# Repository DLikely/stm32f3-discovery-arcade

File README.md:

#STM32F3-Discovery Arcade control interface

An arcade controls interface board implementing a multireport USB HID device with 4
Joysticks connected by GPIO to an STM32F3 Discovery board.

This application is forked from the cjheath's
[stm32f3-discovery-usb-example-project](cjheath/stm32f3-discovery-usb-example.git),
which in turn is derived from the template application for the STM32F30x ARM
microcontrollers that compiles with GNU tools.

The template serves as a quick-start for those who do not wish to use an IDE, but rather
develop in a text editor of choice and build from the command line. It is
derived from [mblythe's version](https://github.com/mblythe86/stm32f3-discovery-basic-template),
which also credits other sources.

## Installing

Before building, you should install the GNU compiler tools.  I'm using the
ARM-supported [Launchpad gcc-arm-embedded](https://launchpad.net/gcc-arm-embedded)
toolchain, installed in **/usr/local/arm**.

The package expects a patched and compiled version of the [STM32F3 standard
peripherals and drivers library](http://www.st.com/web/en/catalog/tools/PF258154)
to be in an adjacent directory. Download the ZIP file, unzip it to the parent
directory above this one, and change into the new **STM32F3-Discovery_FW_V1.1.0**
directory and say:

    patch -p1 < ../stm32f3-discovery-usb-example/STM32F3-Discovery_FW_V1.1.0-gcc.patch

This should cleanly apply the patch to a number of files. Then say:

    make install

This should create an **inst** directory (under the top-level ST firmware
directory) containing two compiled code libraries and copies of all header files
required to build applications.

Now change back to this application template directory and build the application by saying:

    make

You should see five new files whose names start with *main*. These are your
executables and program listings and symbol maps.

##Source code
The **src** directory contains the source-code files for this application template.

**system_stm32f30x.c** can be re-generated using an Excel (.XLS) file developed
by ST. This sets up the system clock values for the project. The file included
in this repository is taken from the STM32F3-Discovery firmware package. It is
copied from the directory: **Libraries/CMSIS/Device/ST/STM32F30x/Source/Templates/**

##Programming and debugging code on the board

First, make sure you have OpenOCD installed and in your path. Then connect your
board, and load the application by saying:

    make program

This task relies on the OpenOCD script provided in the **extra** directory.

To load the program and debug it using GDB in TUI mode, simply say

    make debug

This relies on a gdb script which is also in the **extra** directory.
See [this blog post](http://www.mjblythe.com/hacks/2013/02/debugging-stm32-with-gdb-and-openocd/)
for info about how it works.

##Installing OpenOCD

Assuming you have your ARM gcc tools installed in **/usr/local/arm**, you
probably want to install OpenOCD there too. Change these instructions and the
Makefile if you want it elsewhere. After you have cloned the [OpenOCD
repository](http://openocd.git.sourceforge.net/git/gitweb.cgi?p=openocd/openocd;a=summary),
use these commands to compile and install it (it must be configured with stlink
support enabled):

    ./bootstrap
    ./configure --prefix=/usr/local/arm --enable-maintainer-mode --enable-stlink
    make 
    sudo make install

If there is an error finding the .cfg file, please double-check the
OPENOCD_BOARD_DIR constant in the Makefile.

###UDEV Rule for the Discovery Board

If you are not able to communicate with the STM32F3-Discovery board without
root privileges you should add a udev rule for this hardware by following
[these steps from the stlink repo readme file](https://github.com/texane/stlink#readme).

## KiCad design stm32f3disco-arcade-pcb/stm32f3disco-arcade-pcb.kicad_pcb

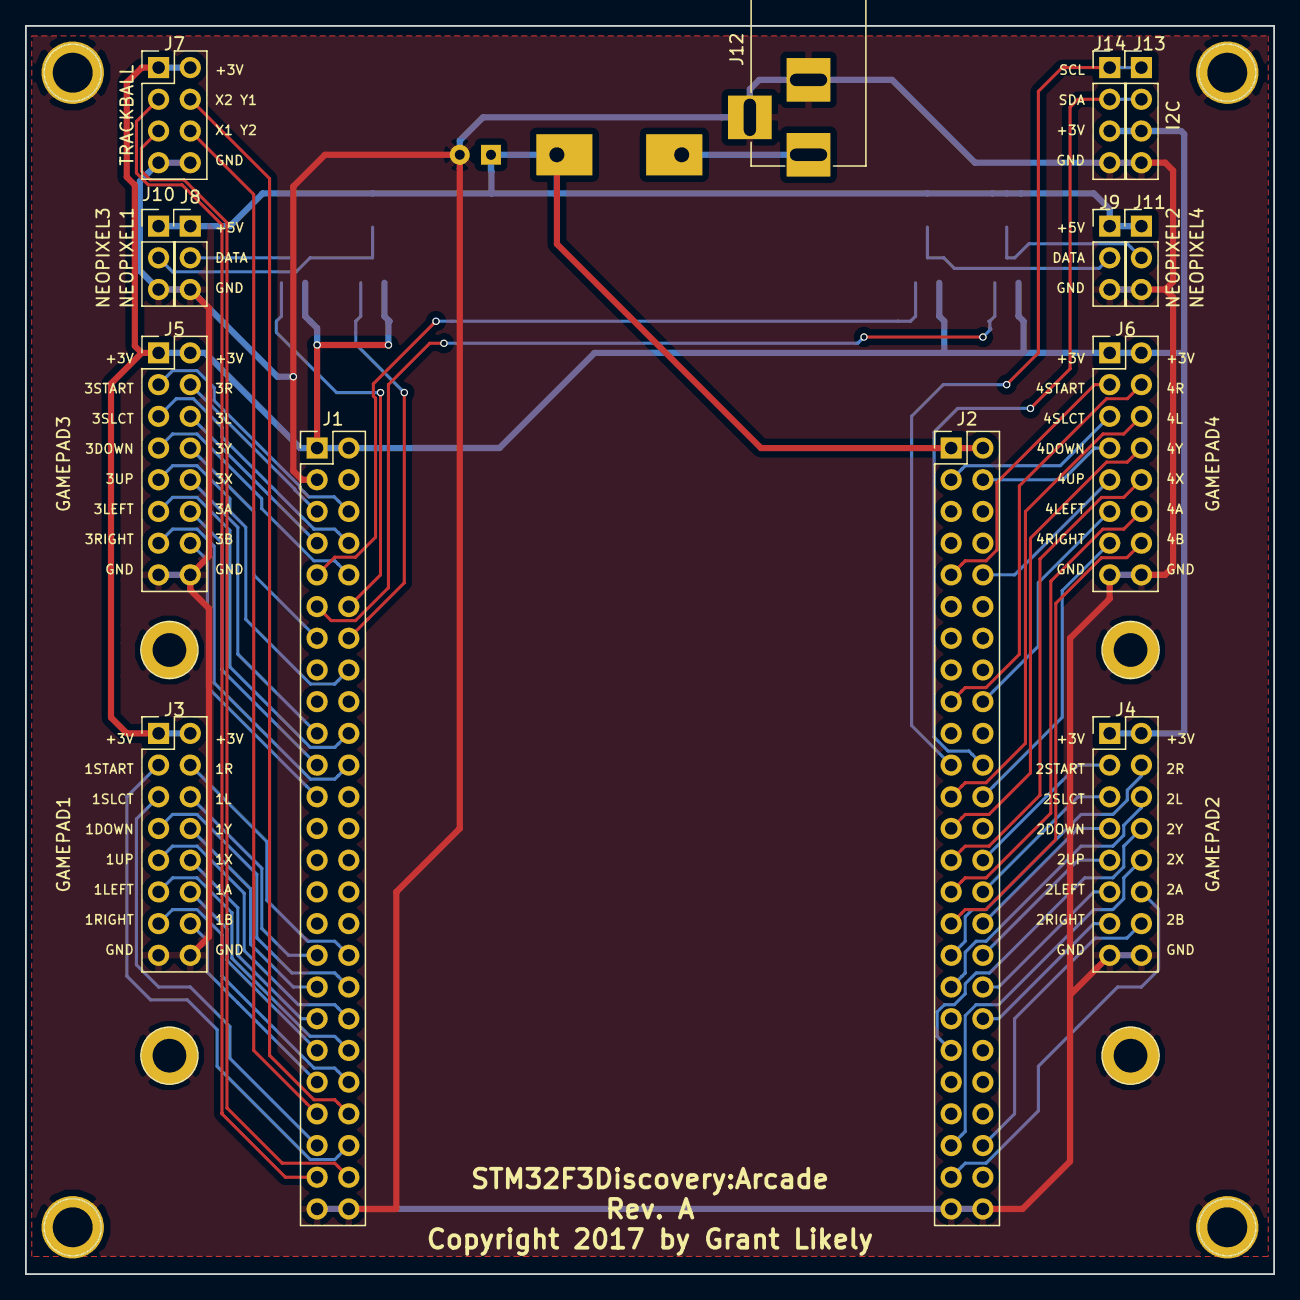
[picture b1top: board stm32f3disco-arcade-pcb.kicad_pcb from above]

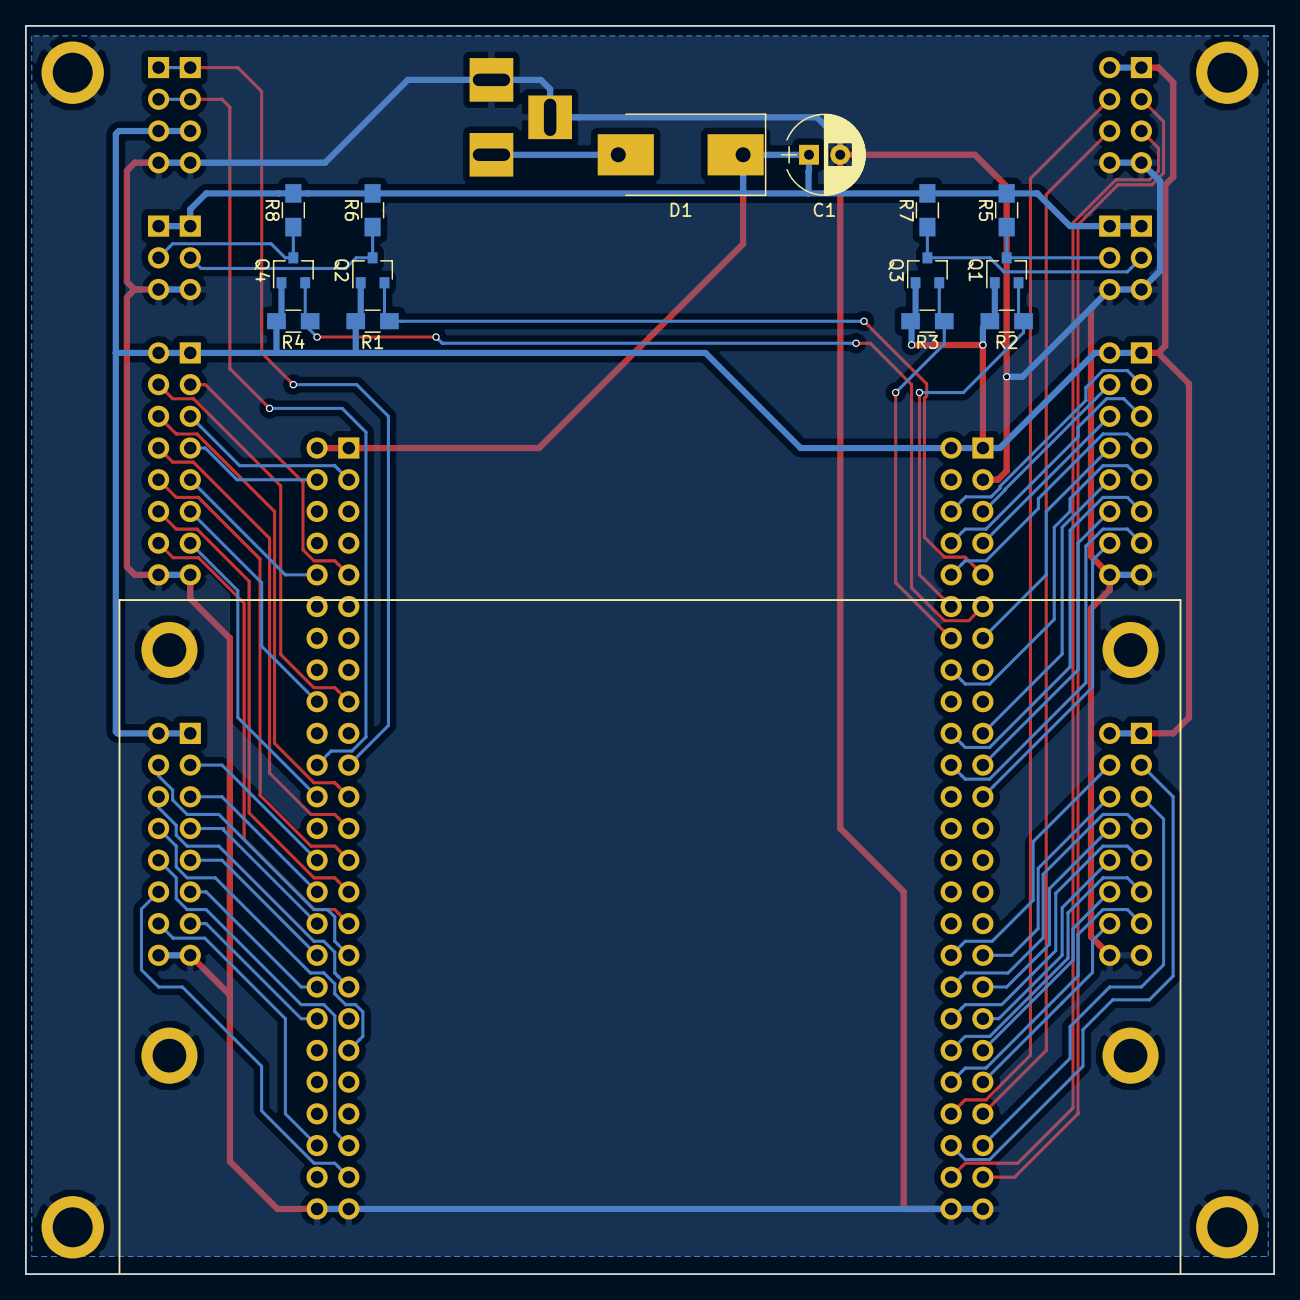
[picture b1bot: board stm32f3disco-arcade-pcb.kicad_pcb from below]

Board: 2 copper layers, 100.0 x 100.0 mm, 36 parts (14 on the bottom side), 66 nets.

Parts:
C1: 1000uF; CP_Radial_D6.3mm_P2.50mm
D1: D; D_SMC-RM10_Universal_Handsoldering
H1, H2, H3, H4: MountingHole_3.2mm_M3; 1pin
H5, H6, H7, H8: MountingHole_2.7mm_M2.5; 1pin
J1: STM32F3DISCO_P1; Pin_Header_Straight_2x25_Pitch2.54mm
J2: STM32F3DISCO_P2; Pin_Header_Straight_2x25_Pitch2.54mm
J3: GAMEPAD1; Pin_Header_Straight_2x08_Pitch2.54mm
J4: GAMEPAD2; Pin_Header_Straight_2x08_Pitch2.54mm
J5: GAMEPAD3; Pin_Header_Straight_2x08_Pitch2.54mm
J6: GAMEPAD4; Pin_Header_Straight_2x08_Pitch2.54mm
J7: TRACKBALL; Pin_Header_Straight_2x04_Pitch2.54mm
J8: NEOPIXEL1; Pin_Header_Straight_1x03_Pitch2.54mm
J9: NEOPIXEL2; Pin_Header_Straight_1x03_Pitch2.54mm
J10: NEOPIXEL3; Pin_Header_Straight_1x03_Pitch2.54mm
J11: NEOPIXEL4; Pin_Header_Straight_1x03_Pitch2.54mm
J12: BARREL_JACK
J13, J14: I2C; Pin_Header_Straight_1x04_Pitch2.54mm
Q1, Q2, Q3, Q4: BSS138; SOT-23
R1, R2, R3, R4, R5, R6, R7, R8: 10k; R_0805_HandSoldering

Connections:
+3V3: J1.1, J1.2, J3.1, J3.2, J4.1, J4.2, J5.1, J5.2, J6.1, J6.2, J7.1, J7.2, J13.3, J14.3, Q1.1, Q2.1, Q3.1, Q4.1, R1.2, R2.2, R3.2, R4.2
+5V: C1.1, D1.1, J2.1, J2.2, J8.1, J9.1, J10.1, J11.1, R5.2, R6.2, R7.2, R8.2
+5VA: D1.2, J12.1
/P1A: J1.41, J3.14
/P1B: J1.39, J3.12
/P1DOWN: J1.36, J3.7
/P1L: J1.33, J3.6
/P1LEFT: J1.40, J3.11
/P1R: J1.34, J3.4
/P1RIGHT: J1.42, J3.13
/P1SLCT: J1.45, J3.5
/P1STRT: J1.46, J3.3
/P1UP: J1.38, J3.9
/P1X: J1.37, J3.10
/P1Y: J1.35, J3.8
/P2A: J2.46, J4.14
/P2B: J2.47, J4.12
/P2DOWN: J2.32, J4.7
/P2L: J2.35, J4.6
/P2LEFT: J2.36, J4.11
/P2R: J2.33, J4.4
/P2RIGHT: J2.38, J4.13
/P2SLCT: J2.30, J4.5
/P2STRT: J2.28, J4.3
/P2UP: J2.34, J4.9
/P2X: J2.45, J4.10
/P2Y: J2.39, J4.8
/P3A: J1.23, J5.14
/P3B: J1.21, J5.12
/P3DOWN: J1.10, J5.7
/P3L: J1.7, J5.6
/P3LEFT: J1.20, J5.11
/P3R: J1.5, J5.4
/P3RIGHT: J1.22, J5.13
/P3SLCT: J1.8, J5.5
/P3STRT: J1.6, J5.3
/P3UP: J1.16, J5.9
/P3X: J1.19, J5.10
/P3Y: J1.13, J5.8
/P4A: J2.31, J6.14
/P4B: J2.29, J6.12
/P4DOWN: J2.4, J6.7
/P4L: J2.23, J6.6
/P4LEFT: J2.18, J6.11
/P4R: J2.17, J6.4
/P4RIGHT: J2.24, J6.13
/P4SLCT: J2.3, J6.5
/P4STRT: J2.9, J6.3
/P4UP: J2.10, J6.9
/P4X: J2.27, J6.10
/P4Y: J2.25, J6.8
GND: C1.2, H1.1, H2.1, H3.1, H4.1, H5.1, H6.1, H7.1, H8.1, J1.3, J1.49, J1.50, J2.49, J2.50, J3.15, J3.16, J4.15, J4.16, J5.15, J5.16, J6.15, J6.16, J7.7, J7.8, J8.3, J9.3, J10.3, J11.3, J12.2, J12.3, J13.4, J14.4
unnamed: J8.2, Q1.3, R5.1
unnamed: J9.2, Q2.3, R6.1
unnamed: J10.2, Q3.3, R7.1
unnamed: J11.2, Q4.3, R8.1
PWM0: J1.12, Q1.2, R2.1
PWM1: J1.9, Q2.2, R1.1
PWM2: J1.14, Q3.2, R3.1
PWM3: J1.11, Q4.2, R4.1
SCL: J2.21, J13.1, J14.1
SDA: J2.22, J13.2, J14.2
TBALL_X1: J1.48, J7.5
TBALL_X2: J1.47, J7.3
TBALL_Y1: J1.44, J7.4
TBALL_Y2: J1.43, J7.6

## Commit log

2017-09-10 Refactor to provide 4 gamepad interfaces
    Refactored the project to be used as an Arcade control panel interface.
    This commit changes it to be a multireport hid device with 4 GPIO
    connected joysticks. Still to be added is a trackball interface and
    control of WS2812 NeoPixels RGB LEDs.
2017-09-10 Initial support for NeoPixel LED illumination
    Add support for NeoPixels attached to TIM2. This patch just associates
    LEDs with buttons and lights the LED when the button is pressed. Next
    step will be to add output reports for setting the LED state.
2017-09-10 Fix button assignments and Y axis direction
    The y axis was oriented the wrong way. Positive values mean up, not
    down. Also reorder the buttons to match the Buffalo gamepad. Button
    order is now: A,B,X,Y,L,R,Select,Start.
2017-09-10 Add trackball support with TIM3/4 quatrature mode
    Enable TIM3 and TIM4 in encoder mode to use as a mouse, and add another
    report ID for the mouse reports. The joystick pins were also moved to
    free up the pins attached to TIM3/4. This change is reflected in main.c
2017-09-10 Update README to describe the arcade interface project
2017-09-10 Default to button LEDs being on instead of off.
    Change default to light all the LEDs, and to turn them off when the
    associated button is pressed.
2017-09-10 Add PCB KiCad project
    This is an adaptor PCB design for the STM32F3-Discovery board to make
    wiring up arcade controls simpler and tidier, as well as allowing for
    external power.
2017-09-10 Set button mappings for stm32f3disco-arcade adapter
    The custom arcade adaptor board is being used now and some of the GPIO pin
    mappings have changed. All the LED mappings have changed too as well as
    being changed to SK6812 RGBW modules. Change the button mapping to match
    the hardware.
2017-09-10 Fix UART pin assignment for STM32F3-Discovery
    The STM32F3 Discovery user manual incorrectly says that USART1 is mapped
    to PA9/10. It is not. It is mapped to PC4/5 instead, which requires a
    change to the board design so that USART console output can be used.
2017-09-10 Add mouse click actions
    Make some of the arcade buttons dual purpose by generating mouse click
    events in addition to button presses. This may be a little hacky, but it
    is a reasonable first step. However, this commit exposes a problem with
    the way event reports are handled. Frequently reports get lost which
    results in lost button presses. This will need to be fixed, probably by
    explicitly waiting for the previous USB report to complete sending
2017-09-10 Add color effect to trackball
    Adds support for illuminating the trackball with a 7-pixel NeoPixel
    'Jewel' daisy chained to end of the player 2 & 4 LED string. As the
    trackball is rolled, the color changes using the common NeoPixel wheel()
    function.
2017-09-10 Fix x-axis polarity on trackball
    It was reversed.
2017-09-10 Enable all 4 NeoPixel channels
    Enable driving NeoPixels on all 4 NeoPixel outputs, aka all 4 output
    channels of TIM1 in PWM mode. The TIM device supports writing to
    multiple registers on each DMA trigger. The driver uses this to load the
    transmit buffer with PWM values for each of the output pins.
    There is still only one buffer for NeoPixel colour data, but now it is
    divided into 4, with each channel assigned a quarter of the buffer. So,
2017-09-10 Add macros to simplify setting LED color and location
    The color and location of buttons can change for each different arcade
    panel build. To make it easier to change the configuration, move the
    values into a new set of #defines at the top of main.c
2017-09-10 Update to RGBW NeoPixels
    Fix the code to work for 32-bit RGBW NeoPixels instead of 24-bit RGB.
    This is a hard-coded fix to get RGBW working. Future change will be to
    make the code runtime configurable between 24 and 32 bit pixels.
2017-09-10 trivial: fix indentation
2017-09-10 Add the Adafruit NeoPixel library to hack on
    The Adafruit NeoPixel library is the most popular API for the pixels,
    and it already supports all the variants. Add the Adafruit code so that
    STM32 support can be added.
2017-09-12 Only refresh gamepad reports when the report can actually be sent
    The gamepad reports were getting refreshed every time through the loop,
    but reports are only generated every 5th time through. To make sure data
    doesn't get dropped, only refresh the report on a cycle when it can
    actually be sent.
2017-09-12 Fix missed reports bug
    Wait for the previous transfer to complete before kicking off another
    one and fix the wait loop so that the main loop doesn't get stuck
    waiting for a particular value of the DataReady timer counter.
2017-09-13 Use a VID/DID pair that sets HID_QUIRK_MULTI_REPORT in Linux
    Linux doesn't handle multiple joystick devices well. It tries to make
    the all a single joystick. Use someone elses VID/DID to get the
    multireport quirk turned on when the device is plugged in.
2017-09-13 Fix y axix polarity (again)
    Repeat after me. Up is negative, down is positive.
    Signed-up-by: Grant Likely <grant.likely@secretlab.ca>
2017-09-16 Fix powerup problem with USB
    Insert a delay on making the USB lines active so that the powerup
    sequence doesn't cause USB to fail to enumerate
2017-09-17 Handle all of the USB HID protocol
    Implement the rest of the HID protocol so that the device responds
    correctly when the host sets/gets idle, and when it fetches the get
    reports.
2017-09-17 Update USB descriptors to better describe the device
    Little changes to the USB HID descriptor.
    - Change max power to 480mA
    - Update HID Spec version to v1.1
    - Change max report size to 8
2017-09-17 Clean up indentation on main.c and add ws2812 header
2017-09-17 Move things around to get rid of main.h
    Nothing from main.c is called from anywhere else. There is no purpose to
    having a main.h. Move the function declarations out of that file and
    delete it. Also move main() to the bottom of main.c so that it doesn't
    need any forward function declarations either.
2017-09-17 Cleanup usb_desc.[ch]
    Clean up the indentation and comments on usb_desc files.
2017-09-17 Move Accelerometer code to another file
2017-09-18 Cleanup usb_prop.[ch] indentation
2017-09-18 Cleanup usb_desc.[ch] to not export as much
    To improve general code sanitation, remove as much as possible from
    usb_desc.h and only export what is necessary.
2017-09-18 Restrict PrevXferComplete to main.c
    main.c is the only place that PrevXferComplete needs to be used.
2017-09-18 Clean up usb_istr.[ch]
2017-09-19 Check the status of all controls every loop
    The main loop was very naively only updating one of the 5 reports every
    time through which is less than ideal. It should be checking all of them
    and making sure every report that has data gets sent out each time
    through.
2017-09-19 Move color helpers to ws2812.h
    The color macros are part of the ws2812.c code. Move it out of main.c
    where it doesn't belong.
2017-09-19 Store color values in a u32
    Use u32 values for storing colors. A u32 is independent from the pixel
    format, and this code needs to support both RGB and RGBW pixels. Using a
    u32 means the color value doesn't change depending on the pixel type.
2017-09-19 Consistently use #defined values with dereferencing pixel data
    Clean up the neopixel buffer references to use a helper function for
    dereferencing specific pixels in the buffer
2017-09-19 Switch to byte-oriented pixel buffer
    Change the code from an array of fixed size pixels to a flat buffer that
    can have the pixels mapped wherever they need to be. This allows both
    RGB and RGBW pixels to be supported at the same time, and even connected
    to the same channel.
2017-09-25 Abstract out neopixel strip properties
    Factor out the neopixel handling that was hard coded into main.c and
    make it a proper set of helper functions. This makes it possible to
    support multiple pixel formats from the same firmware and the main code
    doesn't need to calculate each pixel's offset in the frame buffer.
2017-09-25 Add physical position information about the pixels
    The physical pixel locations will be used to create animations across
    the arcade panel.
2017-09-26 Add a simple RGB animations engine
    Add a simple animation engine for the Neopixels. The engine only knows
    how to do two things. It can display each of the player's assigned
    colours, or it can cycle through the rainbow in a variety of patterns.
    Changing modes is accomplished by pressing the P4 "start & select"
    buttons at the same time.
    There is lots of room to improve the display effects, and it would look
2017-09-30 Add an neopixel metadata initializer macro
    Neopixel location data is divided by 4 so that it will fit in a pair of
    bytes. Rather than dividing every single value manually, use an
    initializer to consistently modify the pixel location.
2017-09-30 Eliminate usb_prop.h to reduce lines of code
    Nothing in usb_prop.c is exported, so having the header file is just
    fluff. Move everything from usb_prop.h into usb_prop.c and reorganize
    the file to eliminate the function declarations.
2017-09-30 usb_prop: Eliminate unnecessary lines
    Cleanup usb_prop by eliminated unnecessary lines and using explicit
    structure initializers. Also removes a few unnecessary functions and
    makes it easier to see how things are initialized.

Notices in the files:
stm32f3disco-arcade-pcb/stm32f3disco-arcade-pcb.kicad_pcb:
Copyright 2017 by Grant Likely
